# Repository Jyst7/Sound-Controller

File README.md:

# Sound-Controller
Simple Pi Pico controlled sound/brighness macropad

I was interested in making a new PCB as I haven't made one in a couple months. I wanted to make something practical that I would use in my daily life, I often found myself annoyed by how many different  enues i had to go through to adjust my bolume and brighness so I decided to fix this problem. I also wanted to showcase the pcb because I always enjoy seeing it so I decided tto not make a case for this device.

Pcb:

Schematic

Wiring:

Case:

| Quantity | Component Description                              |Price  |Links                  |
|----------|----------------------------------------------------|-------|-----------------------|
| 100x     | SK6812 MINI-E                                      |$7    |https://www.aliexpress.com/item/1005005193716172.html|
| 5x       | Rotary encoder switch                              |$4     |https://www.aliexpress.com/item/1005003510208490.html|
| 100x     | SMD 10k Resistor                                   |$3.5     |https://www.aliexpress.com/item/1005006198053993.html|
| 1x       | Pi Pico                                            |$3.5     |https://www.aliexpress.com/item/1005006403553612.html|
| 100x     | 100nF SMD 0805 capacitors                          |$2     |https://www.aliexpress.com/item/1626652703.html|
| 1x       | PCB                                  |$10    |

Total price: $30

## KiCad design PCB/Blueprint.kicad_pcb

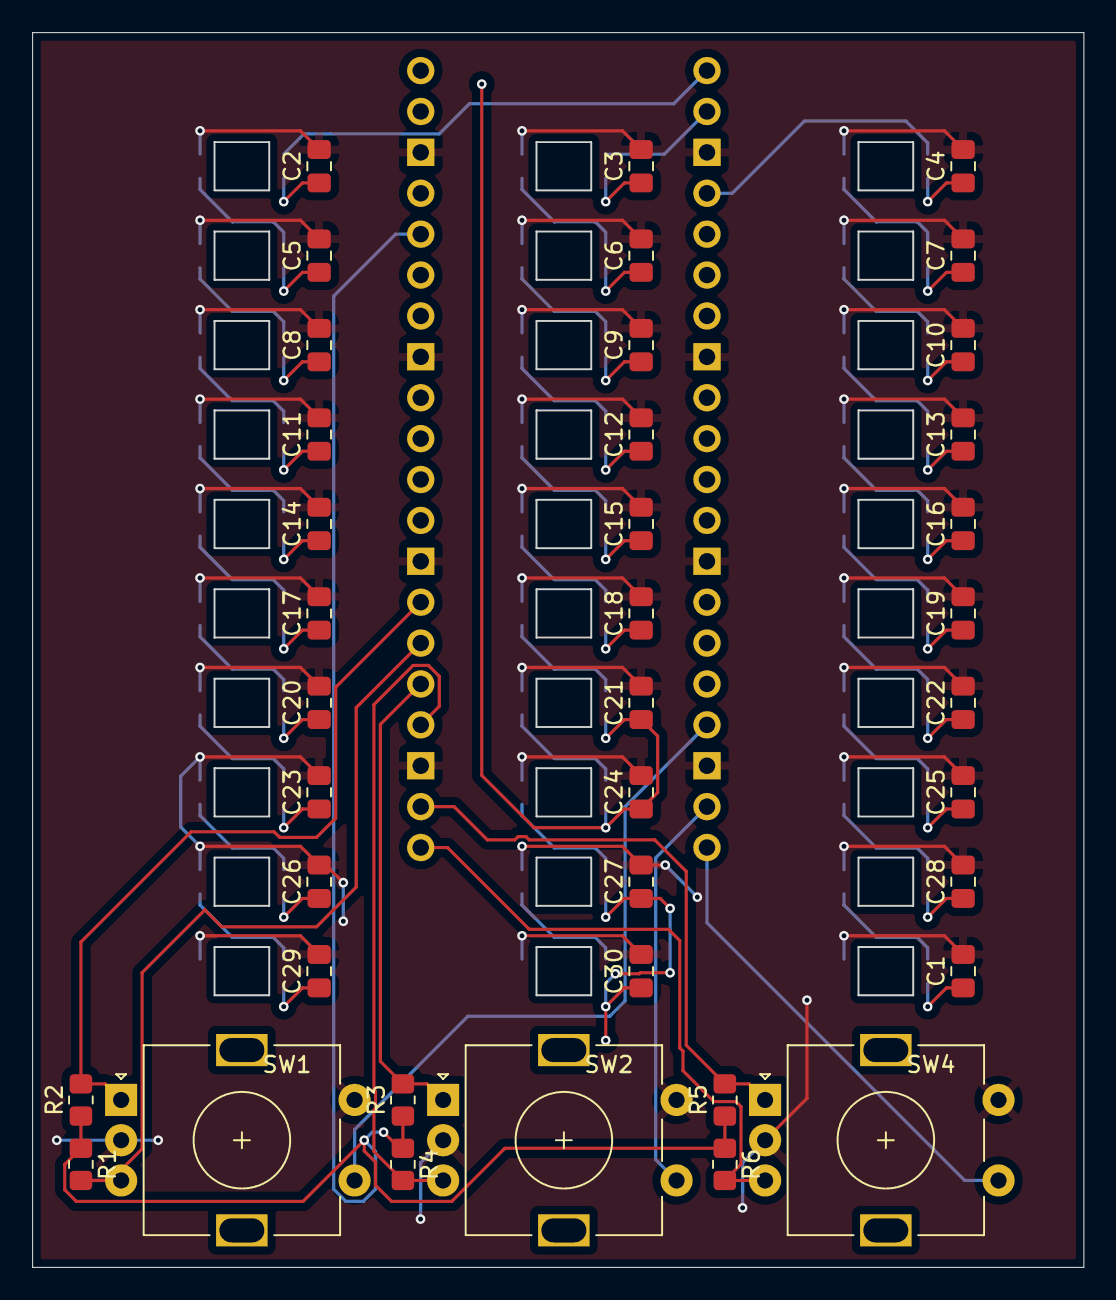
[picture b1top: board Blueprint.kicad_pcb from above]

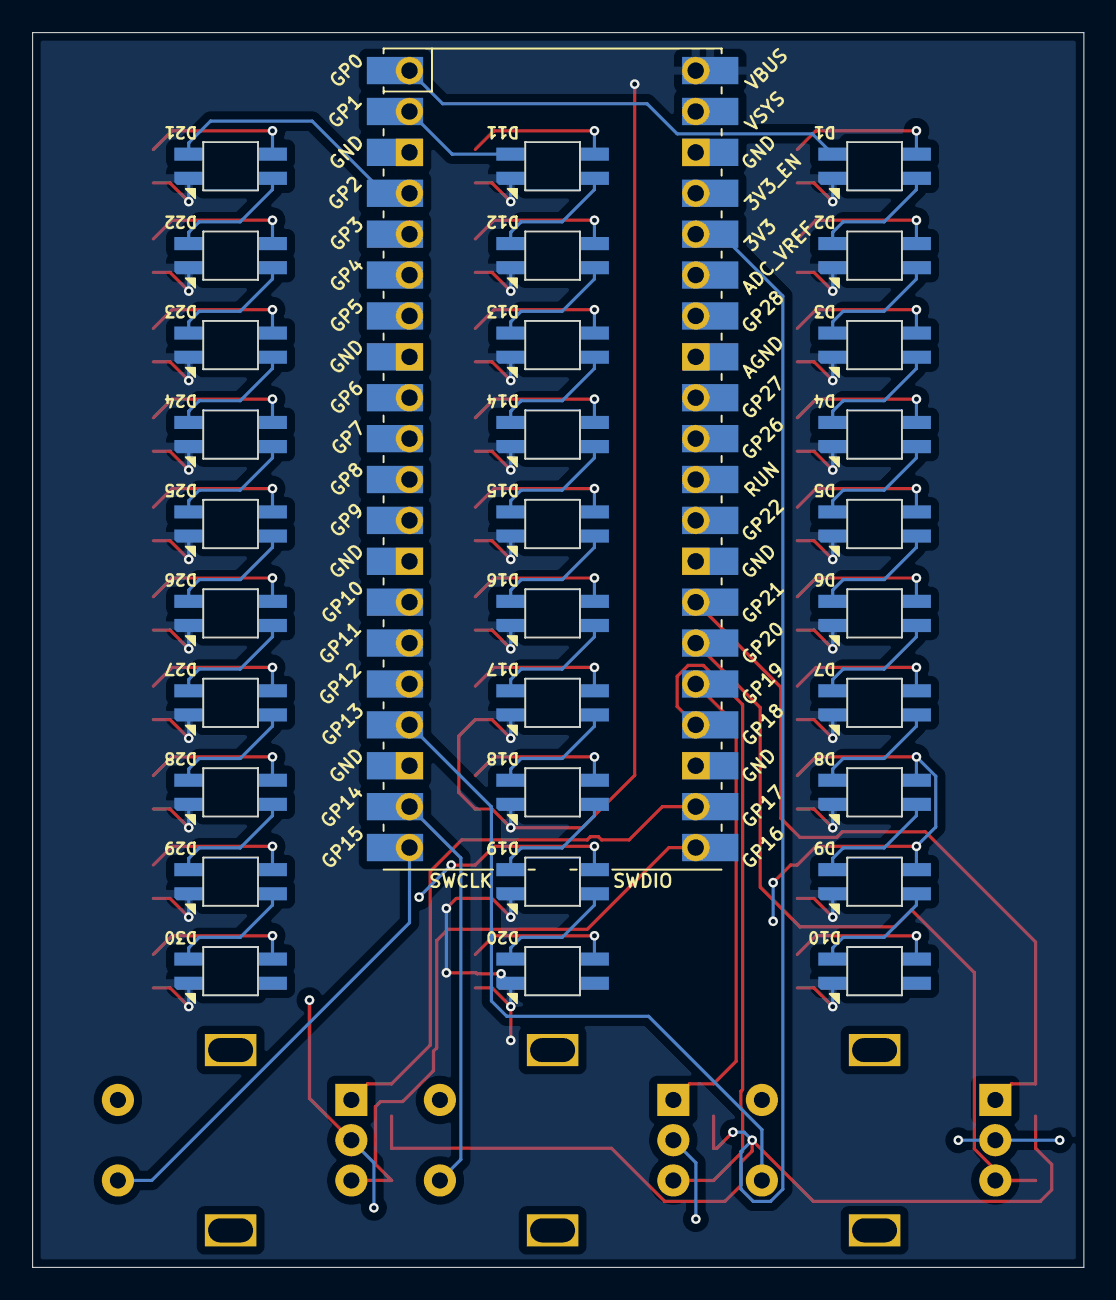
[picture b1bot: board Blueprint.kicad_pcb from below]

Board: 2 copper layers, 65.2 x 76.6 mm, 70 parts (31 on the bottom side), 42 nets.

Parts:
C1, C2, C3, C4, C5, C6, C7, C8, C9, C10, C11, C12, C13, C14, C15, C16, C17, C18, C19, C20, C21, C22, C23, C24, C25, C26, C27, C28, C29, C30: C; C_0805_2012Metric_Pad1.18x1.45mm_HandSolder
D1, D2, D3, D4, D5, D6, D7, D8, D9, D10, D11, D12, D13, D14, D15, D16, D17, D18, D19, D20, D21, D22, D23, D24, D25, D26, D27, D28, D29, D30: SK6812MINI; SK6812MINI-E
R1, R2, R3, R4, R5, R6: R10K; R_0805_2012Metric_Pad1.20x1.40mm_HandSolder
SW1, SW2, SW4: RotaryEncoder_Switch; RotaryEncoder_Alps_EC11E-Switch_Vertical_H20mm
U1: Pico; RPi_Pico_SMD_TH

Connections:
+3.3V: R1.1, R2.1, R3.1, R4.1, R5.1, R6.1, U1.36 (3V3)
+5V: C1.1, C2.1, C3.1, C4.1, C5.1, C6.1, C7.1, C8.1, C9.1, C10.1, C11.1, C12.1, C13.1, C14.1, C15.1, C16.1, C17.1, C18.1, C19.1, C20.1, C21.1, C22.1, C23.1, C24.1, C25.1, C26.1, C27.1, C28.1, C29.1, C30.1, D1.2 (VSS), D2.2 (VSS), D3.2 (VSS), D4.2 (VSS), D5.2 (VSS), D6.2 (VSS), D7.2 (VSS), D8.2 (VSS), D9.2 (VSS), D10.2 (VSS), D11.2 (VSS), D12.2 (VSS), D13.2 (VSS), D14.2 (VSS), D15.2 (VSS), D16.2 (VSS), D17.2 (VSS), D18.2 (VSS), D19.2 (VSS), D20.2 (VSS), D21.2 (VSS), D22.2 (VSS), D23.2 (VSS), D24.2 (VSS), D25.2 (VSS), D26.2 (VSS), D27.2 (VSS), D28.2 (VSS), D29.2 (VSS), D30.2 (VSS), U1.40 (VBUS)
Enc_1A: R2.2, SW1.A, U1.27 (GPIO21)
Enc_1B: R1.2, SW1.B, U1.26 (GPIO20)
Enc_2A: R3.2, SW2.A, U1.25 (GPIO19)
Enc_2B: R4.2, SW2.B, U1.24 (GPIO18)
Enc_3A: R5.2, SW4.A, U1.22 (GPIO17)
Enc_3B: R6.2, SW4.B, U1.21 (GPIO16)
GND: C1.2, C2.2, C3.2, C4.2, C5.2, C6.2, C7.2, C8.2, C9.2, C10.2, C11.2, C12.2, C13.2, C14.2, C15.2, C16.2, C17.2, C18.2, C19.2, C20.2, C21.2, C22.2, C23.2, C24.2, C25.2, C26.2, C27.2, C28.2, C29.2, C30.2, D1.4 (VDD), D2.4 (VDD), D3.4 (VDD), D4.4 (VDD), D5.4 (VDD), D6.4 (VDD), D7.4 (VDD), D8.4 (VDD), D9.4 (VDD), D10.4 (VDD), D11.4 (VDD), D12.4 (VDD), D13.4 (VDD), D14.4 (VDD), D15.4 (VDD), D16.4 (VDD), D17.4 (VDD), D18.4 (VDD), D19.4 (VDD), D20.4 (VDD), D21.4 (VDD), D22.4 (VDD), D23.4 (VDD), D24.4 (VDD), D25.4 (VDD), D26.4 (VDD), D27.4 (VDD), D28.4 (VDD), D29.4 (VDD), D30.4 (VDD), SW1.C, SW1.S2, SW2.C, SW2.S2, SW4.C, SW4.S2, U1.3 (GND), U1.8 (GND), U1.13 (GND), U1.18 (GND), U1.23 (GND), U1.28 (GND), U1.33 (AGND), U1.38 (GND)
LED1: D1.3 (DIN), U1.1 (GPIO0)
LED2: D11.3 (DIN), U1.2 (GPIO1)
LED3: D21.3 (DIN), U1.4 (GPIO2)
unnamed: D1.1 (DOUT), D2.3 (DIN)
unnamed: D2.1 (DOUT), D3.3 (DIN)
unnamed: D3.1 (DOUT), D4.3 (DIN)
unnamed: D4.1 (DOUT), D5.3 (DIN)
unnamed: D5.1 (DOUT), D6.3 (DIN)
unnamed: D6.1 (DOUT), D7.3 (DIN)
unnamed: D7.1 (DOUT), D8.3 (DIN)
unnamed: D8.1 (DOUT), D9.3 (DIN)
unnamed: D9.1 (DOUT), D10.3 (DIN)
unnamed: D11.1 (DOUT), D12.3 (DIN)
unnamed: D12.1 (DOUT), D13.3 (DIN)
unnamed: D13.1 (DOUT), D14.3 (DIN)
unnamed: D14.1 (DOUT), D15.3 (DIN)
unnamed: D15.1 (DOUT), D16.3 (DIN)
unnamed: D16.1 (DOUT), D17.3 (DIN)
unnamed: D17.1 (DOUT), D18.3 (DIN)
unnamed: D18.1 (DOUT), D19.3 (DIN)
unnamed: D19.1 (DOUT), D20.3 (DIN)
unnamed: D21.1 (DOUT), D22.3 (DIN)
unnamed: D22.1 (DOUT), D23.3 (DIN)
unnamed: D23.1 (DOUT), D24.3 (DIN)
unnamed: D24.1 (DOUT), D25.3 (DIN)
unnamed: D25.1 (DOUT), D26.3 (DIN)
unnamed: D26.1 (DOUT), D27.3 (DIN)
unnamed: D27.1 (DOUT), D28.3 (DIN)
unnamed: D28.1 (DOUT), D29.3 (DIN)
unnamed: D29.1 (DOUT), D30.3 (DIN)
SW1: SW1.S1, U1.17 (GPIO13)
SW2: SW2.S1, U1.19 (GPIO14)
SW3: SW4.S1, U1.20 (GPIO15)

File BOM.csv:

"Id";"Designator";"Footprint";"Quantity";"Designation";"Supplier and ref";
1;"D10,D9,D8,D7,D6,D5,D4,D3,D2,D1,D20,D19,D18,D17,D16,D15,D14,D13,D12,D11,D21,D22,D23,D24,D25,D26,D27,D28,D29,D30";"SK6812MINI-E";30;"SK6812MINI";;;
2;"C29,C30,C28,C27,C26,C25,C24,C23,C22,C21,C20,C19,C18,C17,C16,C15,C14,C13,C12,C11,C10,C9,C8,C7,C6,C5,C4,C3,C2,C1";"C_0805_2012Metric_Pad1.18x1.45mm_HandSolder";30;"C";;;
3;"R1,R2,R6,R5,R4,R3";"R_0805_2012Metric_Pad1.20x1.40mm_HandSolder";6;"R10K";;;
4;"SW1,SW2,SW4";"RotaryEncoder_Alps_EC11E-Switch_Vertical_H20mm";3;"RotaryEncoder_Switch";;;
5;"U1";"RPi_Pico_SMD_TH";1;"Pico";;;

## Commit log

2025-10-30 Update JOURNAL.md with 4-Day Macropad project details
    Documented the progress and components for a 4-Day Macropad project, detailing ideas, components, schematic, and PCB creation.
2025-10-30 Rename Blueprint.csv to BOM.csv
2025-10-30 Update README with project images and time log
    Added images and time spent on project.
2025-10-30 Refactor main.py for keyboard configuration
2025-10-30 Add time spent to each journal entry
    Updated journal entries with time spent on each day.
2025-10-30 Enhance README with project details and components
    Added project description, schematic, wiring details, and component list with prices.
2025-10-30 Update quantity of Pi Pico in README
2025-10-30 Update PCB price and total price in README
2025-10-31 Create A
